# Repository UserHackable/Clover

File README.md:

## Clover 

### Board dimensions

* (300000, 240000) original units
* (3.0000, 2.4000) inches
* (76.2000, 60.9600) mm

| Front | Back |
| --- | --- |
|  |  |

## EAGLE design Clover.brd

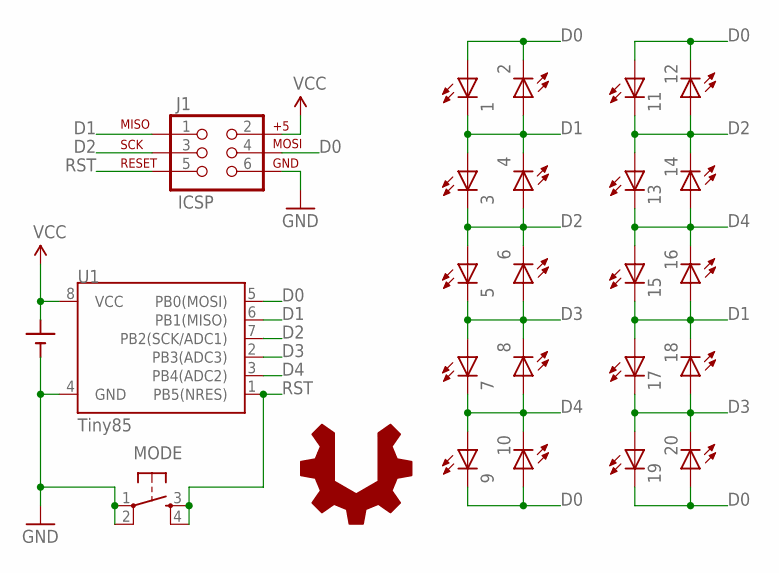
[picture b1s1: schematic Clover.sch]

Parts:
1, 2, 3, 4, 5, 6, 7, 8, 9, 10, 11, 12, 13, 14, 15, 16, 17, 18, 19, 20: LED5MM
BATT: CR2032; CR2032-THRU
J1: ICSP; 2X3-NS
MODE: TAC_SWITCHPTH; TACTILE-PTH
U1: Tiny85; DIP08
U$1: USER_HACKABLE

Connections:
D0: 1.A, 2.K (C), 9.K (C), 10.A, 11.A, 12.K (C), 19.K (C), 20.A, J1.4 (MOSI), U1.5 (PB0(MOSI))
D1: 1.K (C), 2.A, 3.A, 4.K (C), 15.K (C), 16.A, 17.A, 18.K (C), J1.1 (MISO), U1.6 (PB1(MISO))
D2: 3.K (C), 4.A, 5.A, 6.K (C), 11.K (C), 12.A, 13.A, 14.K (C), J1.3 (SCK), U1.7 (PB2(SCK/ADC1))
D3: 5.K (C), 6.A, 7.A, 8.K (C), 17.K (C), 18.A, 19.A, 20.K (C), U1.2 (PB3(ADC3))
D4: 7.K (C), 8.A, 9.A, 10.K (C), 13.K (C), 14.A, 15.A, 16.K (C), U1.3 (PB4(ADC2))
GND: BATT.-, J1.6 (GND), MODE.1, MODE.2, U1.4 (GND)
RST: J1.5 (RST), MODE.3, MODE.4, U1.1 (PB5(NRES))
VCC: BATT.+1 (+), J1.2 (V+), U1.8 (VCC)

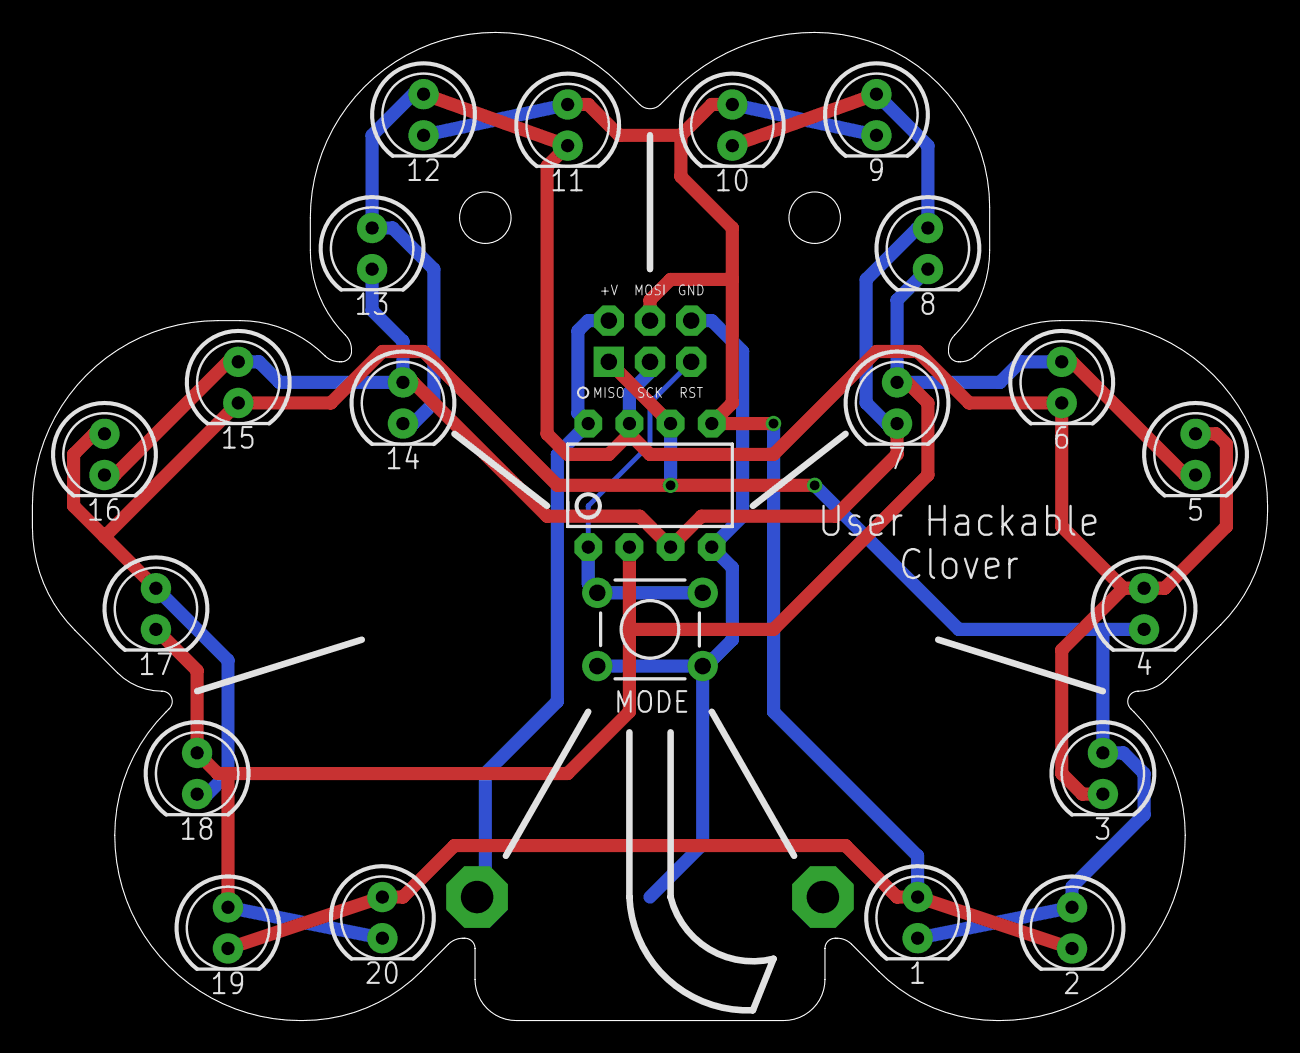
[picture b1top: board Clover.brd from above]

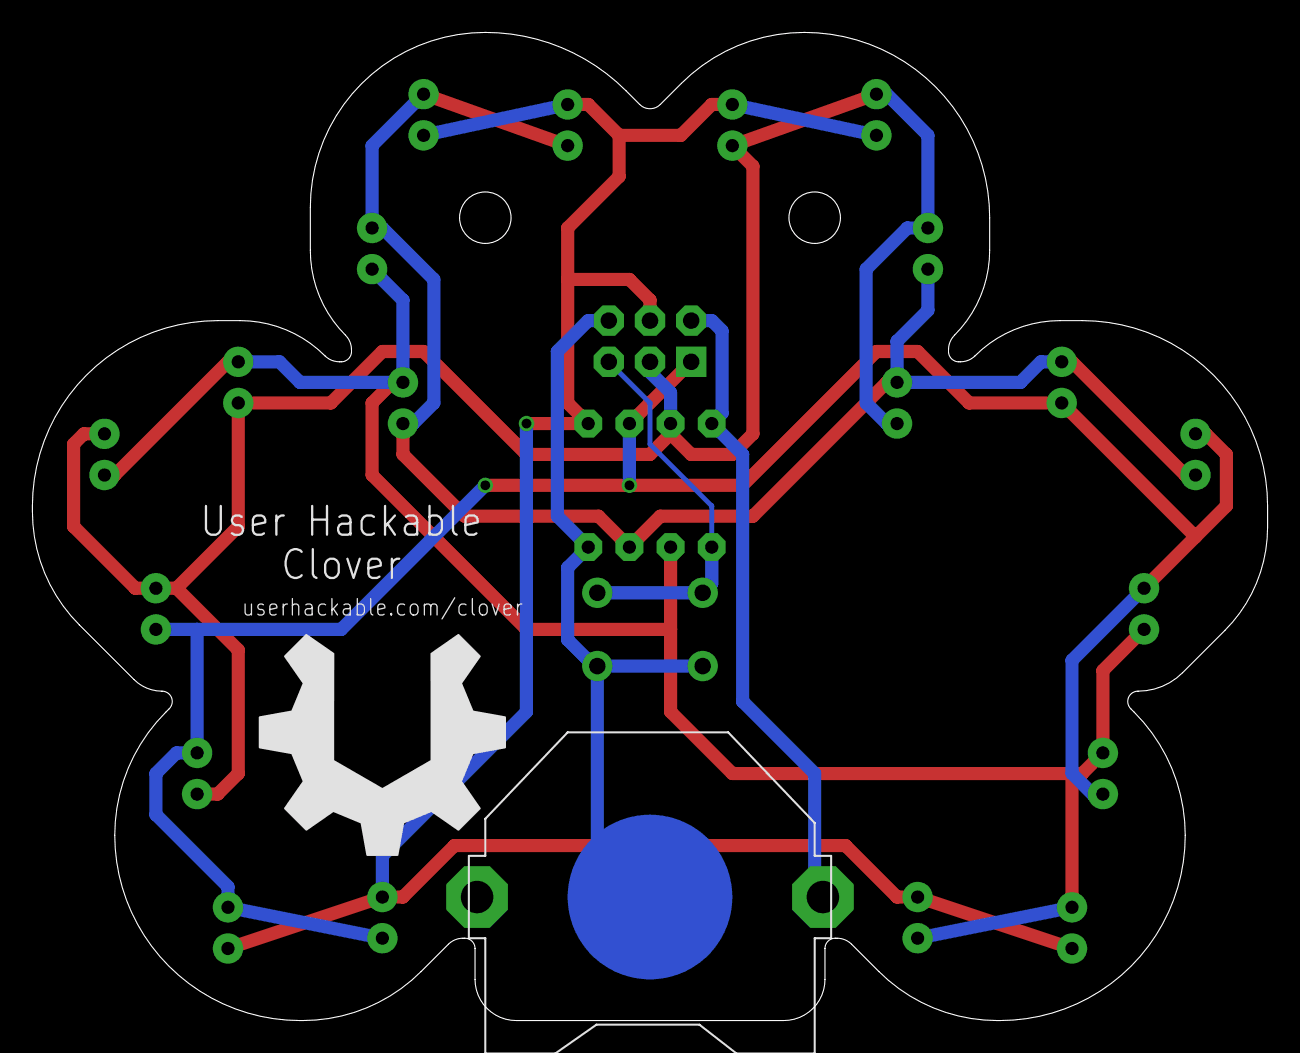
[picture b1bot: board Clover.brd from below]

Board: 2 copper layers, 76.2 x 61.0 mm, 25 parts (2 on the bottom side), 8 nets.

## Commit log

2016-04-06 update images
2016-04-06 cleanup of back image
2016-04-07 from Makefile

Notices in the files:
parts and their libraries:
SparkFun-DigitalIC: Licensing: Creative Commons ShareAlike 4.0 International - https://creativecommons.org/licenses/by-sa/4.0
